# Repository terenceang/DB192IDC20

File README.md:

# DB192IDC20

## A adapter for connecting a Apple UniDisk to an Apple Drive II card

A small adpater to connect an Apple UniDisk with an DB19 connector to a Apple Drive II interface card.
I only using this for an Apple II+, so there is no switching or any kind of drive detection circuits, just a straight pin to pin connection.

Parts.

1. 3D printed shell (Resin Print)
2. DB25F (for harvesting the pins)
3. IDC20 connector
4. PCB

Note. the shell is resin printed with Siraya Tech Blu.
=======
Note. the shell is resin printed with Siraya Tech Blu.

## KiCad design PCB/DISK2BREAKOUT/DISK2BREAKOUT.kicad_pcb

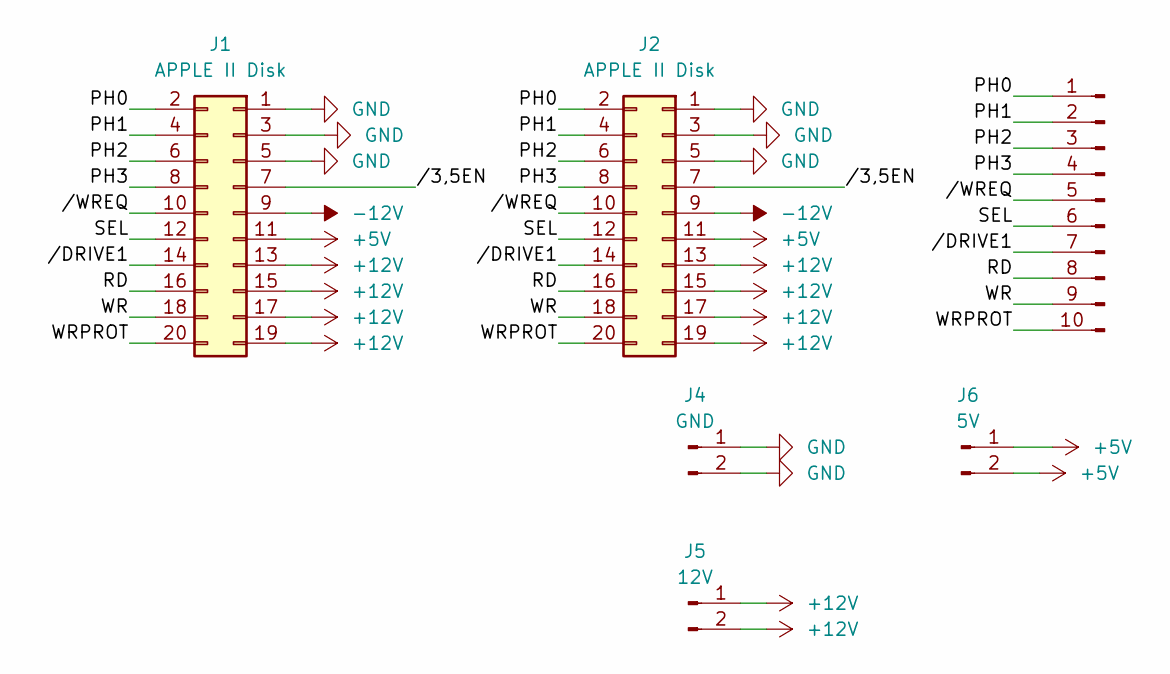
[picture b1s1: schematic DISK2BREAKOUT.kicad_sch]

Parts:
J1, J2: APPLE II Disk; IDC-Header_2x10_P2.54mm_Vertical
J3: Conn_01x10_Male; PinHeader_1x10_P2.54mm_Vertical
J4: GND; PinHeader_1x02_P2.54mm_Vertical
J5: 12V; PinHeader_1x02_P2.54mm_Vertical
J6: 5V; PinHeader_1x02_P2.54mm_Vertical

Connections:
+5V: J1.11, J2.11, J6.1, J6.2
+12V: J1.13, J1.15, J1.17, J1.19, J2.13, J2.15, J2.17, J2.19, J5.1, J5.2
-12V: J1.9, J2.9
/PH0: J1.2, J2.2, J3.1
/PH1: J1.4, J2.4, J3.2
/PH2: J1.6, J2.6, J3.3
/PH3: J1.8, J2.8, J3.4
/RD: J1.16, J2.16, J3.8
/SEL: J1.12, J2.12, J3.6
/WR: J1.18, J2.18, J3.9
/WRPROT: J1.20, J2.20, J3.10
//3,5EN: J1.7, J2.7
//DRIVE1: J1.14, J2.14, J3.7
//WREQ: J1.10, J2.10, J3.5
GND: J1.1, J1.3, J1.5, J2.1, J2.3, J2.5, J4.1, J4.2

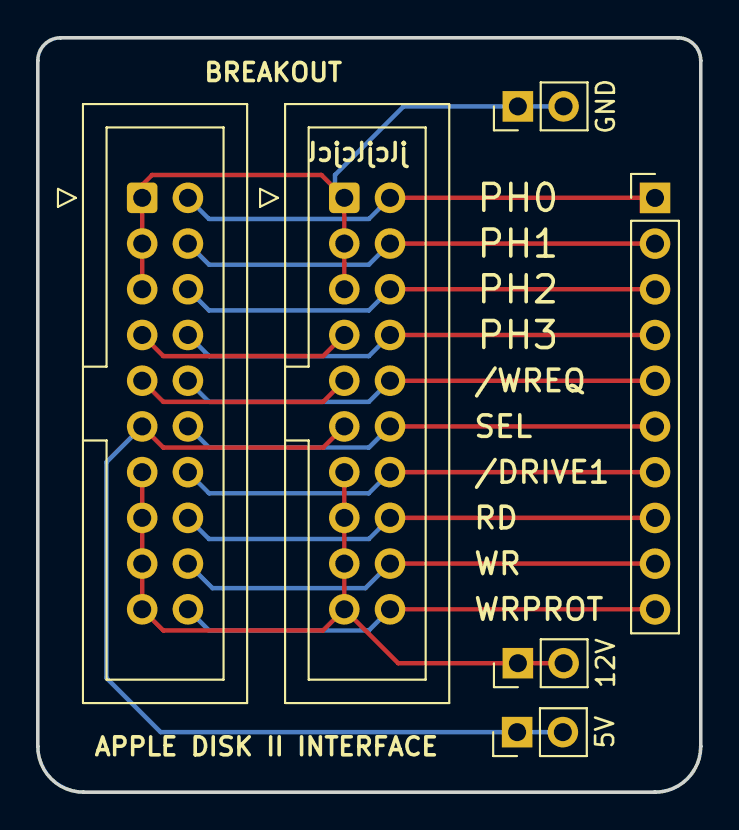
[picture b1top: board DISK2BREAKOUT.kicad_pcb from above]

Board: 2 copper layers, 36.8 x 41.9 mm, 6 parts (0 on the bottom side), 15 nets.

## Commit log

2022-03-04 initial
